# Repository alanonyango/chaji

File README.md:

Embedded system with ESP32 via ESP-IDF for connected IoT and energy-management applications, and the STM32 via STM32CubeIDE for real-time control and power electronics.

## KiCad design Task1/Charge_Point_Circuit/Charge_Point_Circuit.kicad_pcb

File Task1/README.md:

**Kconfig Option Table**

menu "Example Configuration"

&#x20;   config ESP\_WIFI\_SSID

&#x20;       string "WiFi SSID"

&#x20;       default "myssid"

&#x20;       help

&#x20;           SSID (network name) for the example to connect to.

&#x20;   config ESP\_WIFI\_PASSWORD

&#x20;       string "WiFi Password"

&#x20;       default "mypassword"

&#x20;       help

&#x20;           WiFi password (WPA or WPA2) for the example to use.

&#x20;   choice ESP\_WIFI\_SAE\_MODE

&#x20;       prompt "WPA3 SAE mode selection"

&#x20;       default ESP\_STATION\_EXAMPLE\_WPA3\_SAE\_PWE\_BOTH

&#x20;       help

&#x20;           Select mode for SAE as Hunt and Peck, H2E or both.

&#x20;       config ESP\_STATION\_EXAMPLE\_WPA3\_SAE\_PWE\_HUNT\_AND\_PECK

&#x20;           bool "HUNT AND PECK"

&#x20;       config ESP\_STATION\_EXAMPLE\_WPA3\_SAE\_PWE\_HASH\_TO\_ELEMENT

&#x20;           bool "H2E"

&#x20;           depends on ESP\_WIFI\_ENABLE\_SAE\_H2E

&#x20;       config ESP\_STATION\_EXAMPLE\_WPA3\_SAE\_PWE\_BOTH

&#x20;           bool "BOTH"

&#x20;           depends on ESP\_WIFI\_ENABLE\_SAE\_H2E

&#x20;   endchoice

&#x20;   config ESP\_WIFI\_PW\_ID

&#x20;       string "PASSWORD IDENTIFIER"

&#x20;       depends on  ESP\_STATION\_EXAMPLE\_WPA3\_SAE\_PWE\_HASH\_TO\_ELEMENT|| ESP\_STATION\_EXAMPLE\_WPA3\_SAE\_PWE\_BOTH

&#x20;       default ""

&#x20;       help

&#x20;           password identifier for SAE H2E

&#x20;   config ESP\_MAXIMUM\_RETRY

&#x20;       int "Maximum retry"

&#x20;       default 5

&#x20;       help

&#x20;           Set the Maximum retry to avoid station reconnecting to the AP unlimited when the AP is really inexistent.

&#x20;   choice ESP\_WIFI\_SCAN\_AUTH\_MODE\_THRESHOLD

&#x20;       prompt "WiFi Scan auth mode threshold"

&#x20;       default ESP\_WIFI\_AUTH\_WPA2\_PSK

&#x20;       help

&#x20;           The weakest authmode to accept in the scan mode.

&#x20;           This value defaults to ESP\_WIFI\_AUTH\_WPA2\_PSK in case password is present and ESP\_WIFI\_AUTH\_OPEN is used.

&#x20;           Please select ESP\_WIFI\_AUTH\_WEP/ESP\_WIFI\_AUTH\_WPA\_PSK in case AP is operating in WEP/WPA mode.

&#x20;       config ESP\_WIFI\_AUTH\_OPEN

&#x20;           bool "OPEN"

&#x20;       config ESP\_WIFI\_AUTH\_WEP

&#x20;           bool "WEP"

&#x20;       config ESP\_WIFI\_AUTH\_WPA\_PSK

&#x20;           bool "WPA PSK"

&#x20;       config ESP\_WIFI\_AUTH\_WPA2\_PSK

&#x20;           bool "WPA2 PSK"

&#x20;       config ESP\_WIFI\_AUTH\_WPA\_WPA2\_PSK

&#x20;           bool "WPA/WPA2 PSK"

&#x20;       config ESP\_WIFI\_AUTH\_WPA3\_PSK

&#x20;           bool "WPA3 PSK"

&#x20;       config ESP\_WIFI\_AUTH\_WPA2\_WPA3\_PSK

&#x20;           bool "WPA2/WPA3 PSK"

&#x20;       config ESP\_WIFI\_AUTH\_WAPI\_PSK

&#x20;           bool "WAPI PSK"

&#x20;   endchoice

endmenu

MQTT Topic: chaji/charger/mcu1/status

Wokwi: https://wokwi.com/projects/458437642617944065

**Schematic**

Components
1. ESP32-WROOM-32
2. AMS117-3.3
3. CP2102
4. BC817 Transistor x3
5. Capacitors
6. Resistors

The circuit was designed around the ESP32‑WROOM‑32 microcontroller as the main controller. A AMS1117‑3.3 voltage regulator converts the input supply to a stable 3.3 V rail required by the ESP32 and other logic components, with capacitor values selected according to the regulator datasheet for stability. A CP2102 USB-to-UART converter provides USB programming and serial communication with the ESP32. Three BC817 transistors are used as switching drivers for external control signals. All resistor and capacitor values were selected based on the respective component datasheets to ensure proper biasing, signal integrity, and stable power regulation.

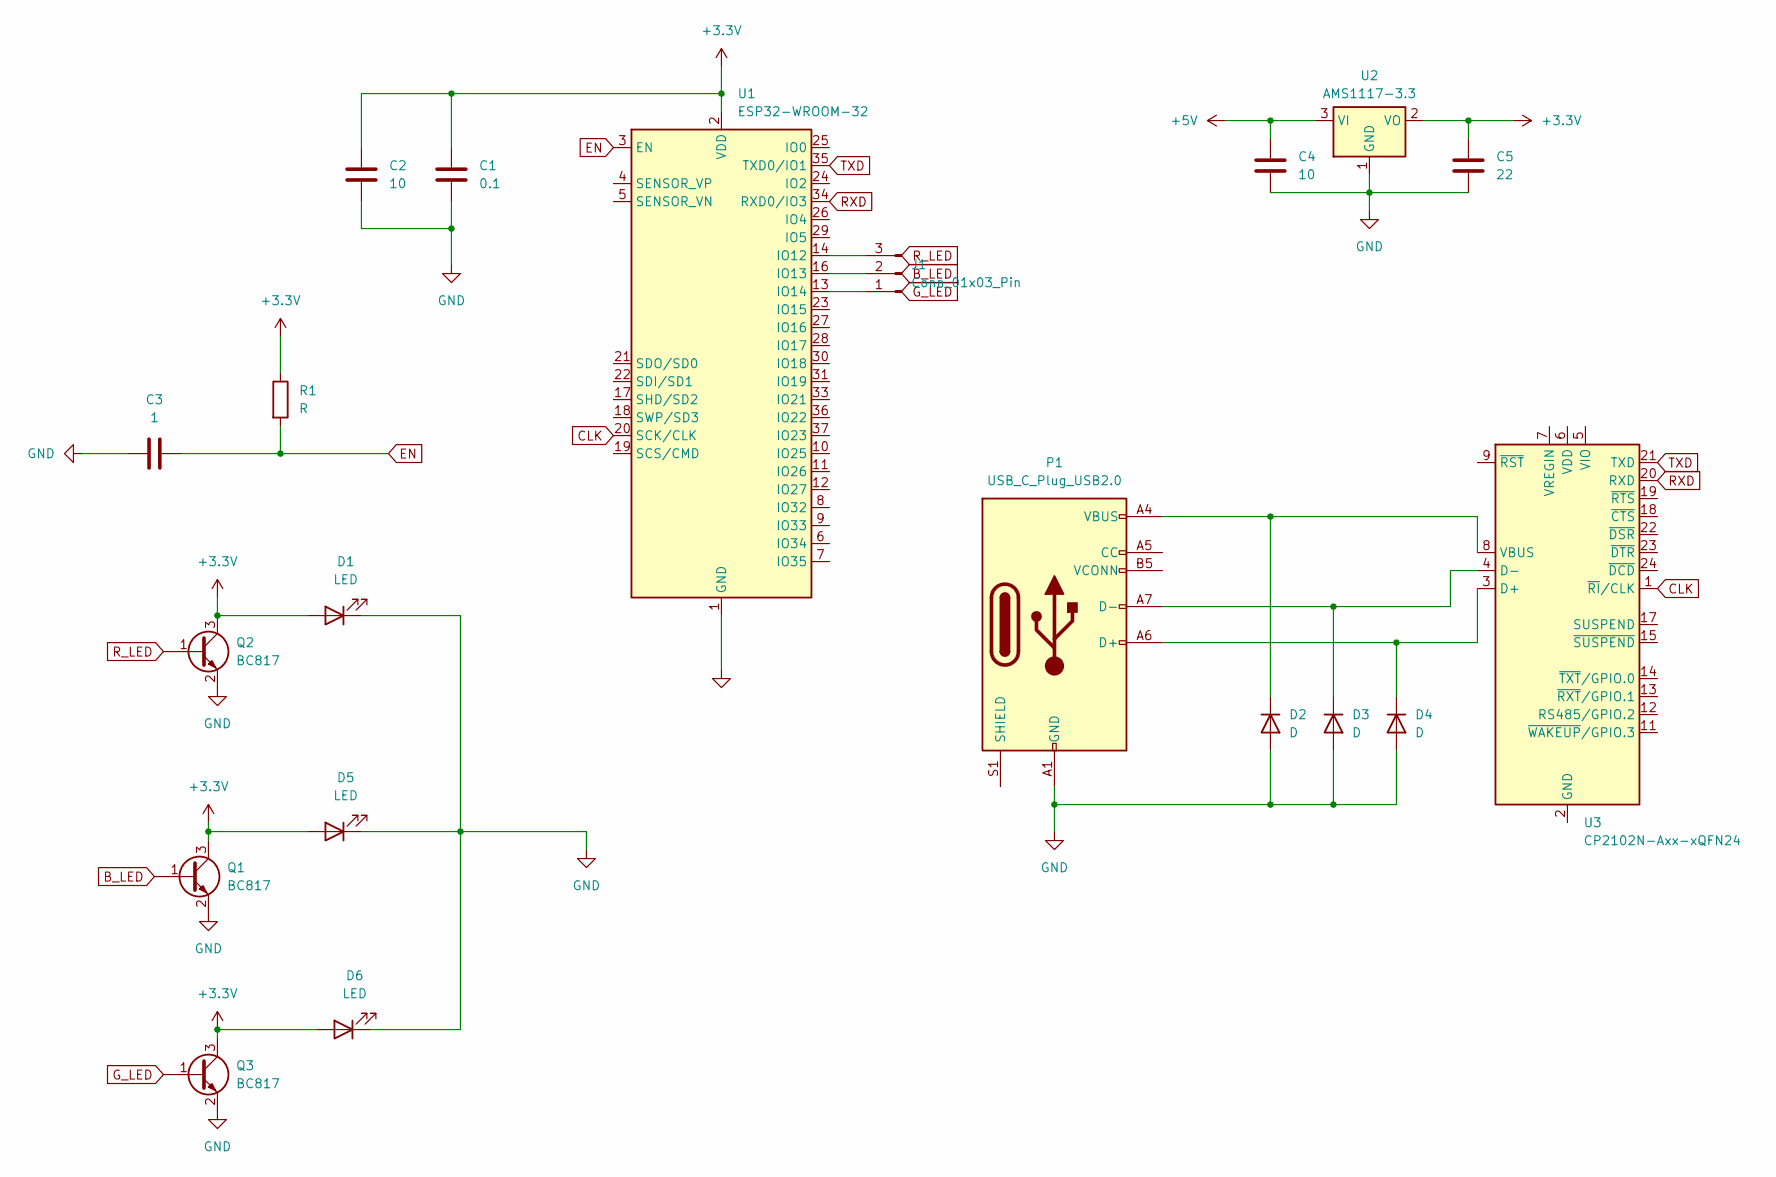
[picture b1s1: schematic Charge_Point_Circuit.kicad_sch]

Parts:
C1: 0.1; C_0201_0603Metric
C2, C4: 10; C_0201_0603Metric
C3: 1; C_0201_0603Metric
C5: 22; C_0201_0603Metric
D1, D5, D6: LED; LED_0201_0603Metric
D2, D3, D4: D; D_0201_0603Metric
J1: Conn_01x03_Pin; PinHeader_1x03_P1.00mm_Vertical
P1: USB_C_Plug_USB2.0; USB_C_Receptacle_GCT_USB4105-xx-A_16P_TopMnt_Horizontal
Q1, Q2, Q3: BC817; SOT-23
R1: R; R_0201_0603Metric
U1: ESP32-WROOM-32
U2: AMS1117-3.3; SOT-223-3_TabPin2
U3: CP2102N-Axx-xQFN24; QFN-24-1EP_4x4mm_P0.5mm_EP2.6x2.6mm

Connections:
+3.3V: C1.1, C2.1, C5.2, D1.2 (A), D5.2 (A), D6.2 (A), Q1.3 (C), Q2.3 (C), Q3.3 (C), R1.1, U1.2 (VDD), U2.2 (VO)
+5V: C4.2, U2.3 (VI)
B_LED: Q1.1 (B)
CLK: U1.20 (SCK/CLK), U3.1 (~RI/CLK)
EN: C3.1, R1.2, U1.3 (EN)
GND: C1.2, C2.2, C3.2, C4.1, C5.1, D1.1 (K), D2.2 (A), D3.2 (A), D4.2 (A), D5.1 (K), D6.1 (K), P1.A1 (GND), P1.A12 (GND), P1.B1 (GND), P1.B12 (GND), Q1.2 (E), Q2.2 (E), Q3.2 (E), U1.1 (GND), U1.15 (GND), U1.38 (GND), U1.39 (GND), U2.1 (GND)
G_LED: Q3.1 (B)
unnamed: D2.1 (K), P1.A4 (VBUS), P1.A9 (VBUS), P1.B4 (VBUS), P1.B9 (VBUS), U3.8 (VBUS)
unnamed: D3.1 (K), P1.A7 (D-), U3.4 (D-)
unnamed: D4.1 (K), P1.A6 (D+), U3.3 (D+)
unnamed: J1.1, U1.13 (IO14)
unnamed: J1.2, U1.16 (IO13)
unnamed: J1.3, U1.14 (IO12)
unnamed: U3.2 (GND), U3.25 (GND)
RXD: U1.34 (RXD0/IO3), U3.20 (RXD)
R_LED: Q2.1 (B)
TXD: U1.35 (TXD0/IO1), U3.21 (TXD)

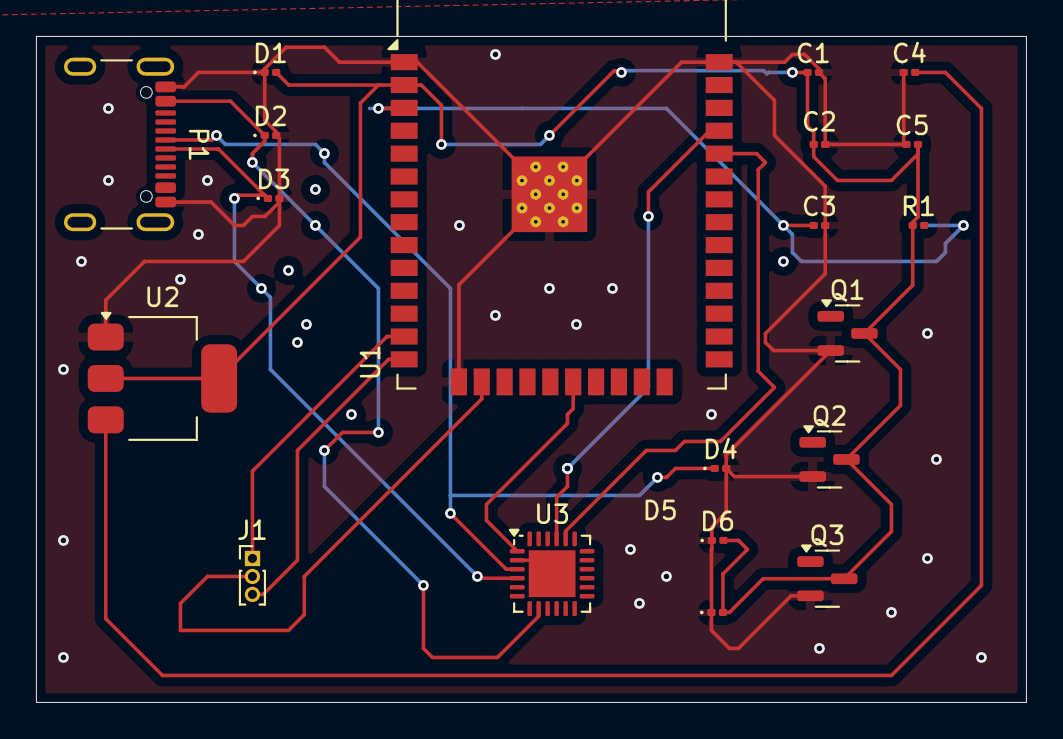
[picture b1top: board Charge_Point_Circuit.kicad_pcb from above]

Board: 2 copper layers, 55.0 x 37.0 mm, 20 parts (0 on the bottom side), 14 nets.

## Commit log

2026-03-14 README.md
